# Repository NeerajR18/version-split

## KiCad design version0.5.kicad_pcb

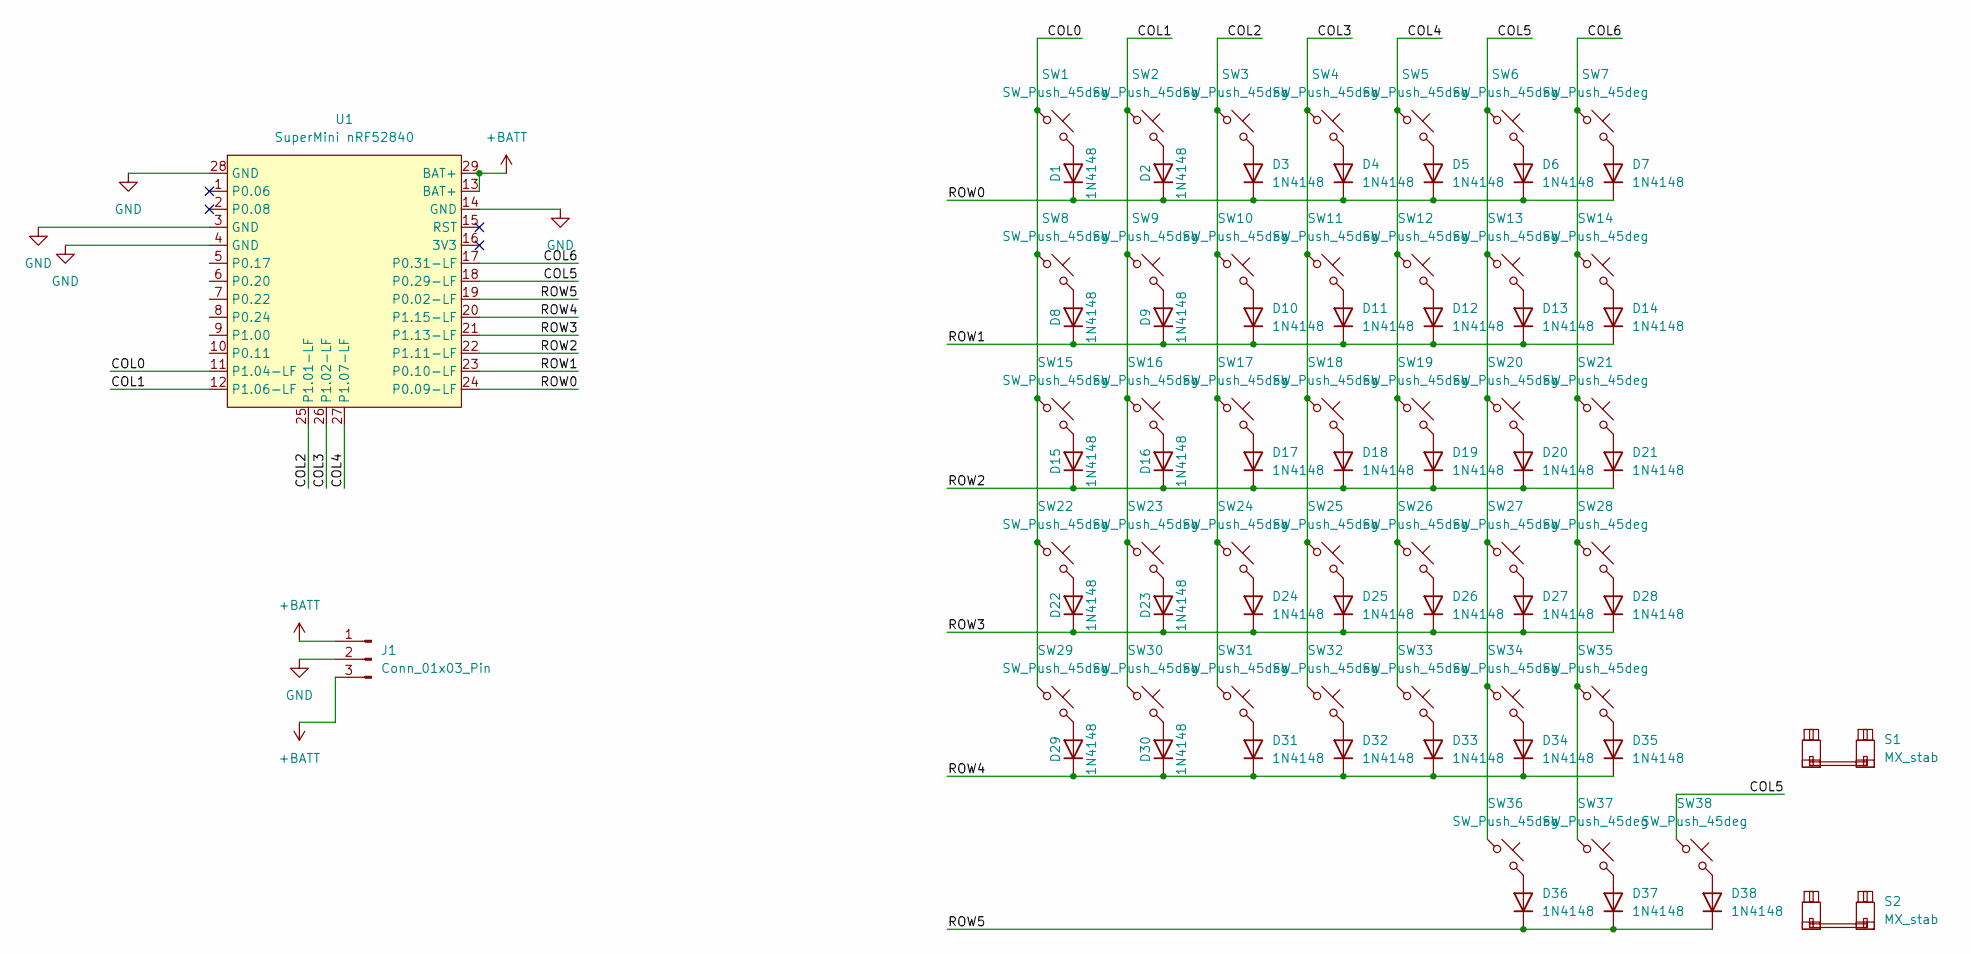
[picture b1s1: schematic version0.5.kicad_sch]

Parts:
D1, D2, D3, D4, D5, D6, D7, D8, D9, D10, D11, D12, D13, D14, D15, D16, D17, D18, D19, D20, D21, D22, D23, D24, D25, D26, D27, D28, D29, D30, D31, D32, D33, D34, D35, D36, D37, D38: 1N4148; D_DO-35_SOD27_P7.62mm_Horizontal
J1: Conn_01x03_Pin; PinHeader_1x03_P2.54mm_Vertical
S1, S2: MX_stab; STAB_MX_2u
SW1, SW2, SW3, SW4, SW5, SW6, SW7, SW8, SW9, SW10, SW11, SW12, SW13, SW14, SW15, SW16, SW17, SW18, SW19, SW20, SW21, SW22, SW23, SW24, SW25, SW26, SW27, SW28, SW29, SW30, SW31, SW32, SW33, SW34, SW35, SW36, SW37, SW38: SW_Push_45deg; Choc_Hotswap
U1: SuperMini nRF52840; SuperMini_nRF52840_AH_USBup

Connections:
+BATT: J1.1, J1.3, U1.13 (BAT+), U1.29 (BAT+)
/COL0: SW1.1, SW8.1, SW15.1, SW22.1, SW29.1, U1.11 (P1.04-LF)
/COL1: SW2.1, SW9.1, SW16.1, SW23.1, SW30.1, U1.12 (P1.06-LF)
/COL2: SW3.1, SW10.1, SW17.1, SW24.1, SW31.1, U1.25 (P1.01-LF)
/COL3: SW4.1, SW11.1, SW18.1, SW25.1, SW32.1, U1.26 (P1.02-LF)
/COL4: SW5.1, SW12.1, SW19.1, SW26.1, SW33.1, U1.27 (P1.07-LF)
/COL5: SW6.1, SW13.1, SW20.1, SW27.1, SW34.1, SW36.1, SW38.1, U1.18 (P0.29-LF)
/COL6: SW7.1, SW14.1, SW21.1, SW28.1, SW35.1, SW37.1, U1.17 (P0.31-LF)
/ROW0: D1.1 (K), D2.1 (K), D3.1 (K), D4.1 (K), D5.1 (K), D6.1 (K), D7.1 (K), U1.24 (P0.09-LF)
/ROW1: D8.1 (K), D9.1 (K), D10.1 (K), D11.1 (K), D12.1 (K), D13.1 (K), D14.1 (K), U1.23 (P0.10-LF)
/ROW2: D15.1 (K), D16.1 (K), D17.1 (K), D18.1 (K), D19.1 (K), D20.1 (K), D21.1 (K), U1.22 (P1.11-LF)
/ROW3: D22.1 (K), D23.1 (K), D24.1 (K), D25.1 (K), D26.1 (K), D27.1 (K), D28.1 (K), U1.21 (P1.13-LF)
/ROW4: D29.1 (K), D30.1 (K), D31.1 (K), D32.1 (K), D33.1 (K), D34.1 (K), D35.1 (K), U1.20 (P1.15-LF)
/ROW5: D36.1 (K), D37.1 (K), D38.1 (K), U1.19 (P0.02-LF)
GND: J1.2, U1.3 (GND), U1.4 (GND), U1.14 (GND), U1.28 (GND)
unnamed: D1.2 (A), SW1.2
unnamed: D2.2 (A), SW2.2
unnamed: D3.2 (A), SW3.2
unnamed: D4.2 (A), SW4.2
unnamed: D5.2 (A), SW5.2
unnamed: D6.2 (A), SW6.2
unnamed: D7.2 (A), SW7.2
unnamed: D8.2 (A), SW8.2
unnamed: D9.2 (A), SW9.2
unnamed: D10.2 (A), SW10.2
unnamed: D11.2 (A), SW11.2
unnamed: D12.2 (A), SW12.2
unnamed: D13.2 (A), SW13.2
unnamed: D14.2 (A), SW14.2
unnamed: D15.2 (A), SW15.2
unnamed: D16.2 (A), SW16.2
unnamed: D17.2 (A), SW17.2
unnamed: D18.2 (A), SW18.2
unnamed: D19.2 (A), SW19.2
unnamed: D20.2 (A), SW20.2
unnamed: D21.2 (A), SW21.2
unnamed: D22.2 (A), SW22.2
unnamed: D23.2 (A), SW23.2
unnamed: D24.2 (A), SW24.2
unnamed: D25.2 (A), SW25.2
unnamed: D26.2 (A), SW26.2
unnamed: D27.2 (A), SW27.2
unnamed: D28.2 (A), SW28.2
unnamed: D29.2 (A), SW29.2
unnamed: D30.2 (A), SW30.2
unnamed: D31.2 (A), SW31.2
unnamed: D32.2 (A), SW32.2
unnamed: D33.2 (A), SW33.2
unnamed: D34.2 (A), SW34.2
unnamed: D35.2 (A), SW35.2
unnamed: D36.2 (A), SW36.2
unnamed: D37.2 (A), SW37.2
unnamed: D38.2 (A), SW38.2

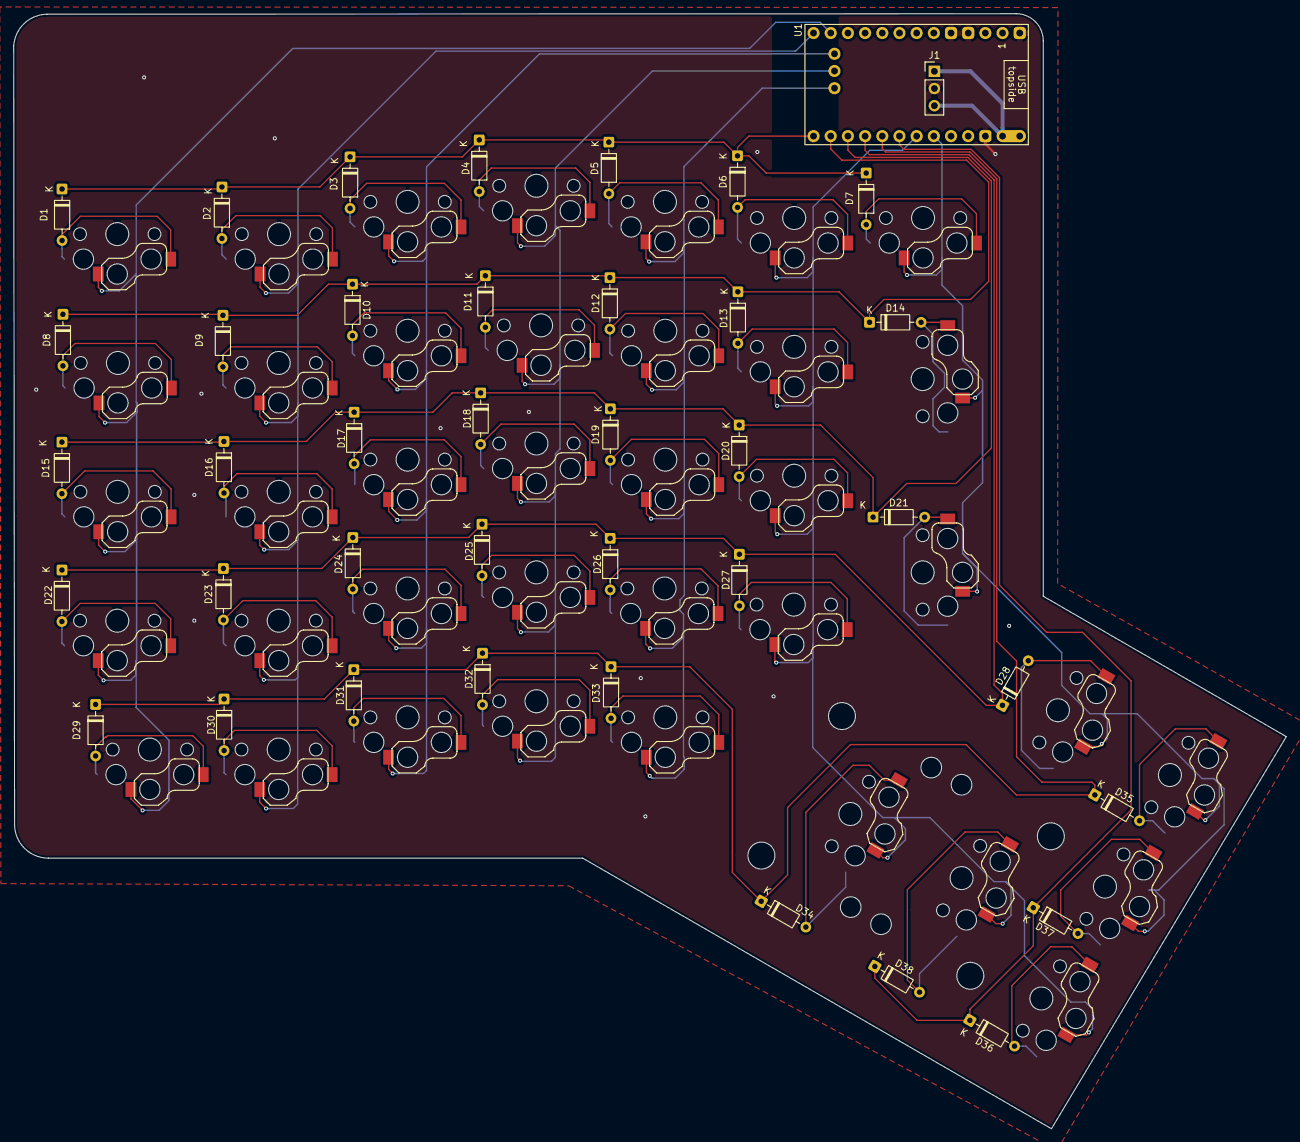
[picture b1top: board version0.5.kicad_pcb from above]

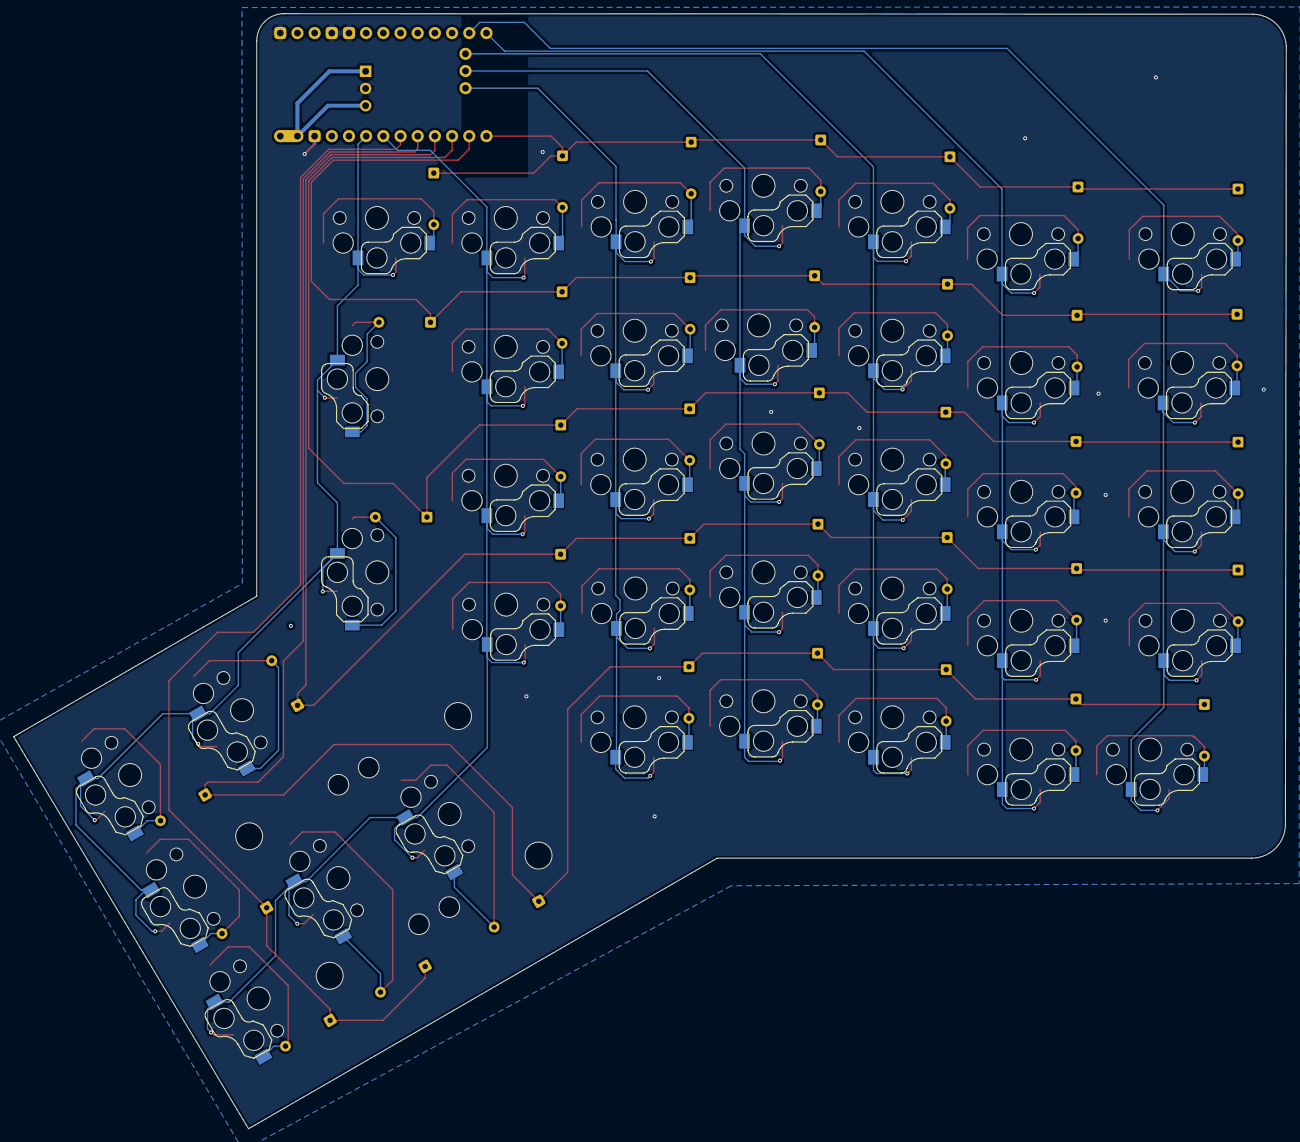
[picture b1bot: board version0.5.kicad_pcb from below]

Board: 2 copper layers, 188.1 x 164.8 mm, 80 parts (2 on the bottom side), 53 nets.

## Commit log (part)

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2026-06-19 Added pcb files
